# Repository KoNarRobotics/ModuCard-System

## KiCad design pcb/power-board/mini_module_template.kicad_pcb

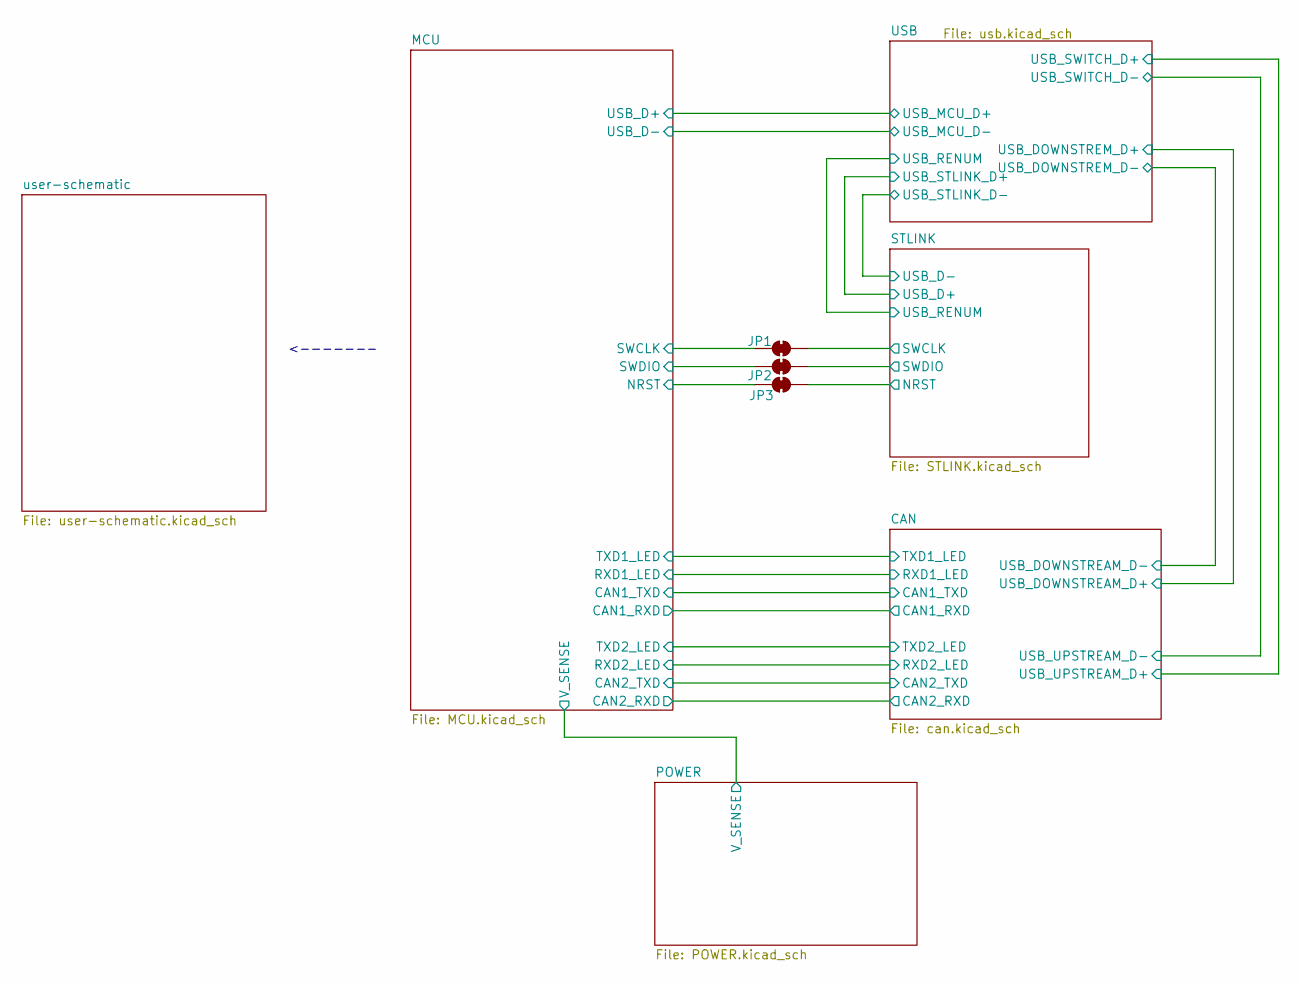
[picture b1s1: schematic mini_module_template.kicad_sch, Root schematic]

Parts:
JP1, JP2, JP3: SolderJumper_2_Bridged; SolderJumper-2_P1.3mm_Open_RoundedPad1.0x1.5mm

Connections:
/MCU/NRST: JP3.1 (A); also elsewhere on the board
/MCU/SWCLK: JP1.1 (A); also elsewhere on the board
/MCU/SWDIO: JP2.1 (A); also elsewhere on the board
/STLINK/NRST: JP3.2 (B); also elsewhere on the board
/STLINK/SWCLK: JP1.2 (B); also elsewhere on the board
/STLINK/SWDIO: JP2.2 (B); also elsewhere on the board

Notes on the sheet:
<-------

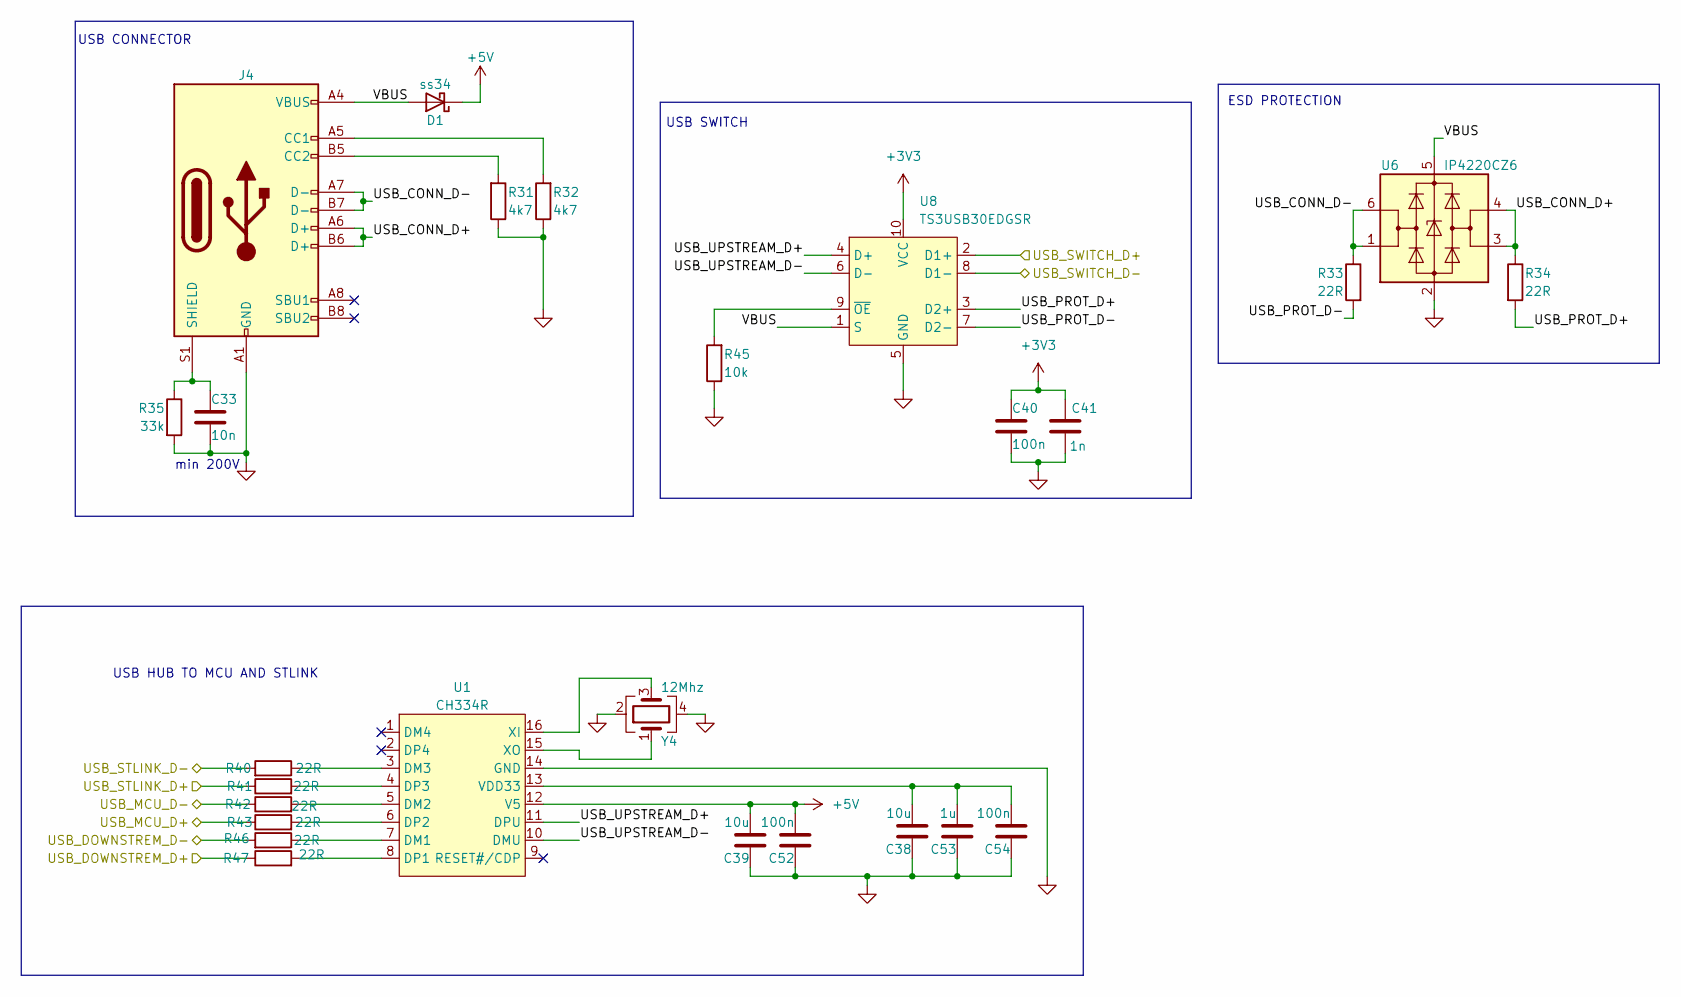
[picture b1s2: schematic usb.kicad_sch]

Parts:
C33: 10n; C_0402_1005Metric
C38, C39: 10u; C_0603_1608Metric
C40, C54: 100n; C_0402_1005Metric
C41: 1n; C_0402_1005Metric
C52: 100n; C_0603_1608Metric
C53: 1u; C_0603_1608Metric
D1: ss34; D_SMA
J4: USB_C_Receptacle_USB2.0; USB_C_Receptacle_G-Switch_GT-USB-7010ASV
R31, R32: 4k7; R_0402_1005Metric
R33, R34, R40, R41, R42, R43, R46, R47: 22R; R_0402_1005Metric
R35: 33k; R_0402_1005Metric
R45: 10k; R_0402_1005Metric
U1: CH334R; QSOP-16_3.9x4.9mm_P0.635mm
U6: IP4220CZ6; SOT-23-6
U8: TS3USB30EDGSR; VSSOP-10_3x3mm_P0.5mm
Y4: 12Mhz; Crystal_SMD_3225-4Pin_3.2x2.5mm

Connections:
+3V3: C40.1, C41.1, U8.10 (VCC); also elsewhere on the board
+5V: C39.2, C52.2, D1.1 (K), U1.12 (V5); also elsewhere on the board
/CAN/USB_DOWNSTREAM_D+: R47.1; also elsewhere on the board
/CAN/USB_DOWNSTREAM_D-: R46.2; also elsewhere on the board
/CAN/USB_UPSTREAM_D+: U8.2 (D1+); also elsewhere on the board
/CAN/USB_UPSTREAM_D-: U8.8 (D1-); also elsewhere on the board
/MCU/USB_D+: R43.1; also elsewhere on the board
/MCU/USB_D-: R42.1; also elsewhere on the board
/STLINK/USB_D+: R41.1; also elsewhere on the board
/STLINK/USB_D-: R40.2; also elsewhere on the board
/USB/USB_CONN_D+: J4.A6 (D+), J4.B6 (D+), R34.1, U6.3 (I/O2), U6.4 (I/O2)
/USB/USB_CONN_D-: J4.A7 (D-), J4.B7 (D-), R33.1, U6.1 (I/O1), U6.6 (I/O1)
/USB/USB_PROT_D+: R34.2, U8.3 (D2+)
/USB/USB_PROT_D-: R33.2, U8.7 (D2-)
/USB/USB_UPSTREAM_D+: U1.11 (DPU), U8.4 (D+)
/USB/USB_UPSTREAM_D-: U1.10 (DMU), U8.6 (D-)
/USB/VBUS: D1.2 (A), J4.A4 (VBUS), J4.A9 (VBUS), J4.B4 (VBUS), J4.B9 (VBUS), U6.5 (VBUS), U8.1 (S)
GND: C33.2, C38.1, C39.1, C40.2, C41.2, C52.1, C53.1, C54.1, J4.A1 (GND), J4.A12 (GND), J4.B1 (GND), J4.B12 (GND), R31.1, R32.1, R35.2, R45.1, U1.14 (GND), U6.2 (GND), U8.5 (GND), Y4.2, Y4.4; also elsewhere on the board
unnamed: J4.A5 (CC1), R32.2
unnamed: J4.B5 (CC2), R31.2
unnamed: C33.1, J4.S1 (SHIELD), R35.1
unnamed: R46.1, U1.7 (DM1)
unnamed: R42.2, U1.5 (DM2)
unnamed: R40.1, U1.3 (DM3)
unnamed: R47.2, U1.8 (DP1)
unnamed: R43.2, U1.6 (DP2)
unnamed: R41.2, U1.4 (DP3)
unnamed: C38.2, C53.2, C54.2, U1.13 (VDD33)
unnamed: U1.16 (XI), Y4.3
unnamed: U1.15 (XO), Y4.1
unnamed: R45.2, U8.9 (~OE)

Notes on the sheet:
USB SWITCH
USB CONNECTOR
USB HUB TO MCU AND STLINK
ESD PROTECTION
min 200V

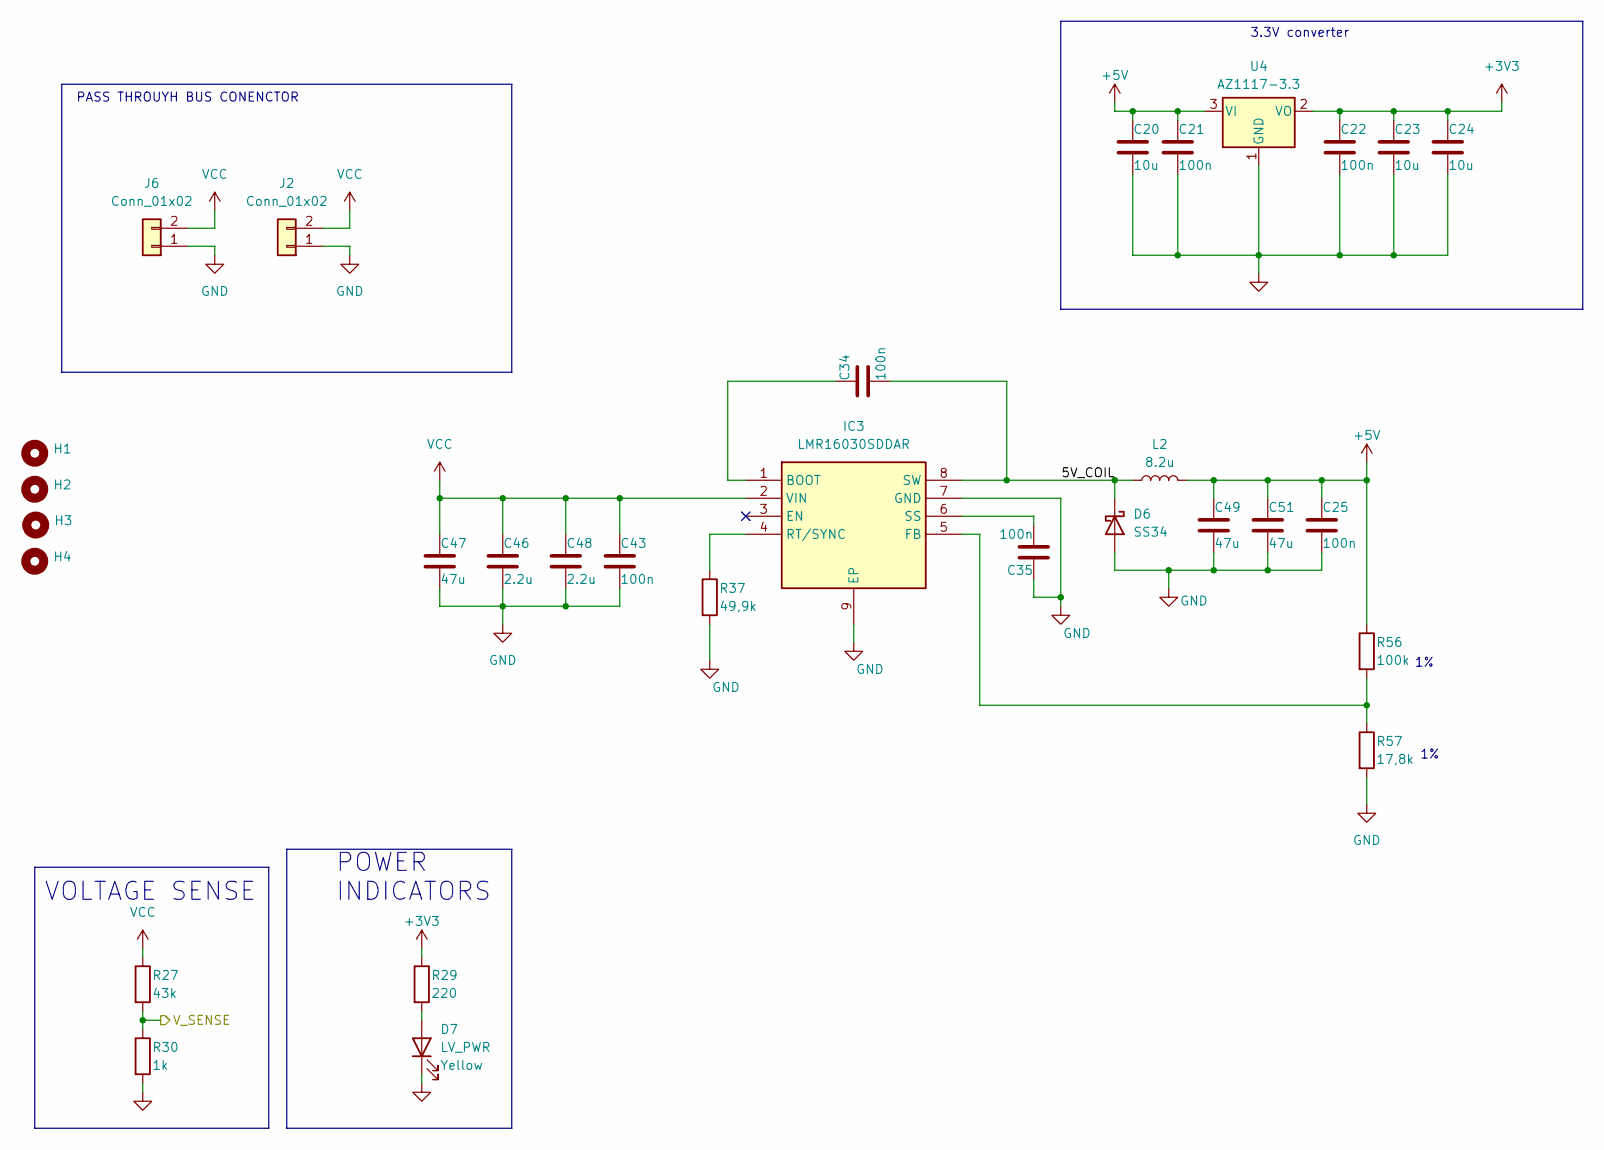
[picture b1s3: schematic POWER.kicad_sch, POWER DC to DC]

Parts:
C20, C23, C24: 10u; C_0805_2012Metric
C21, C25, C34, C35, C43: 100n; C_0402_1005Metric
C22: 100n; C_0603_1608Metric
C46, C48: 2.2u; C_1206_3216Metric
C47: 47u; C_Elec_10x10.2
C49, C51: 47u; C_1206_3216Metric
D6: SS34; D_SMA
D7: LV_PWR; D_0603_1608Metric
H1, H2, H3, H4: MountingHole_3.2mm_M3
IC3: LMR16030SDDAR; SOIC127P600X170-9N; Manufacturer_Part_Number LMR16030SDDAR; Mouser Part Number 595-LMR16030SDDAR
J2, J6: Conn_01x02; AMASS_XT60PW-M_1x02_P7.20mm_Horizontal
L2: 8.2u; L_Cenker_CKCS6045
R27: 43k; R_0402_1005Metric
R29: 220; R_0402_1005Metric
R30: 1k; R_0402_1005Metric
R37: 49,9k; R_0402_1005Metric
R56: 100k; R_0402_1005Metric
R57: 17,8k; R_0402_1005Metric
U4: AZ1117-3.3; SOT-223-3_TabPin2

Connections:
+3V3: C22.1, C23.1, C24.1, R29.1, U4.2 (VO); also elsewhere on the board
+5V: C20.1, C21.1, C25.1, C49.1, C51.1, L2.2, R56.1, U4.3 (VI); also elsewhere on the board
/MCU/V_SENSE: R27.2, R30.1; also elsewhere on the board
/POWER/5V_COIL: C34.2, D6.1 (K), IC3.8 (SW), L2.1
GND: C20.2, C21.2, C22.2, C23.2, C24.2, C25.2, C35.1, C43.2, C46.2, C47.2, C48.2, C49.2, C51.2, D6.2 (A), D7.1 (K), IC3.7 (GND), IC3.9 (EP), J2.1, J6.1, R30.2, R37.2, R57.2, U4.1 (GND); also elsewhere on the board
unnamed: D7.2 (A), R29.2
unnamed: C34.1, IC3.1 (BOOT)
unnamed: IC3.5 (FB), R56.2, R57.1
unnamed: IC3.4 (RT/SYNC), R37.1
unnamed: C35.2, IC3.6 (SS)
VCC: C43.1, C46.1, C47.1, C48.1, IC3.2 (VIN), J2.2, J6.2, R27.1

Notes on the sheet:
VOLTAGE SENSE
PASS THROUYH BUS CONENCTOR
POWER INDICATORS
3.3V converter

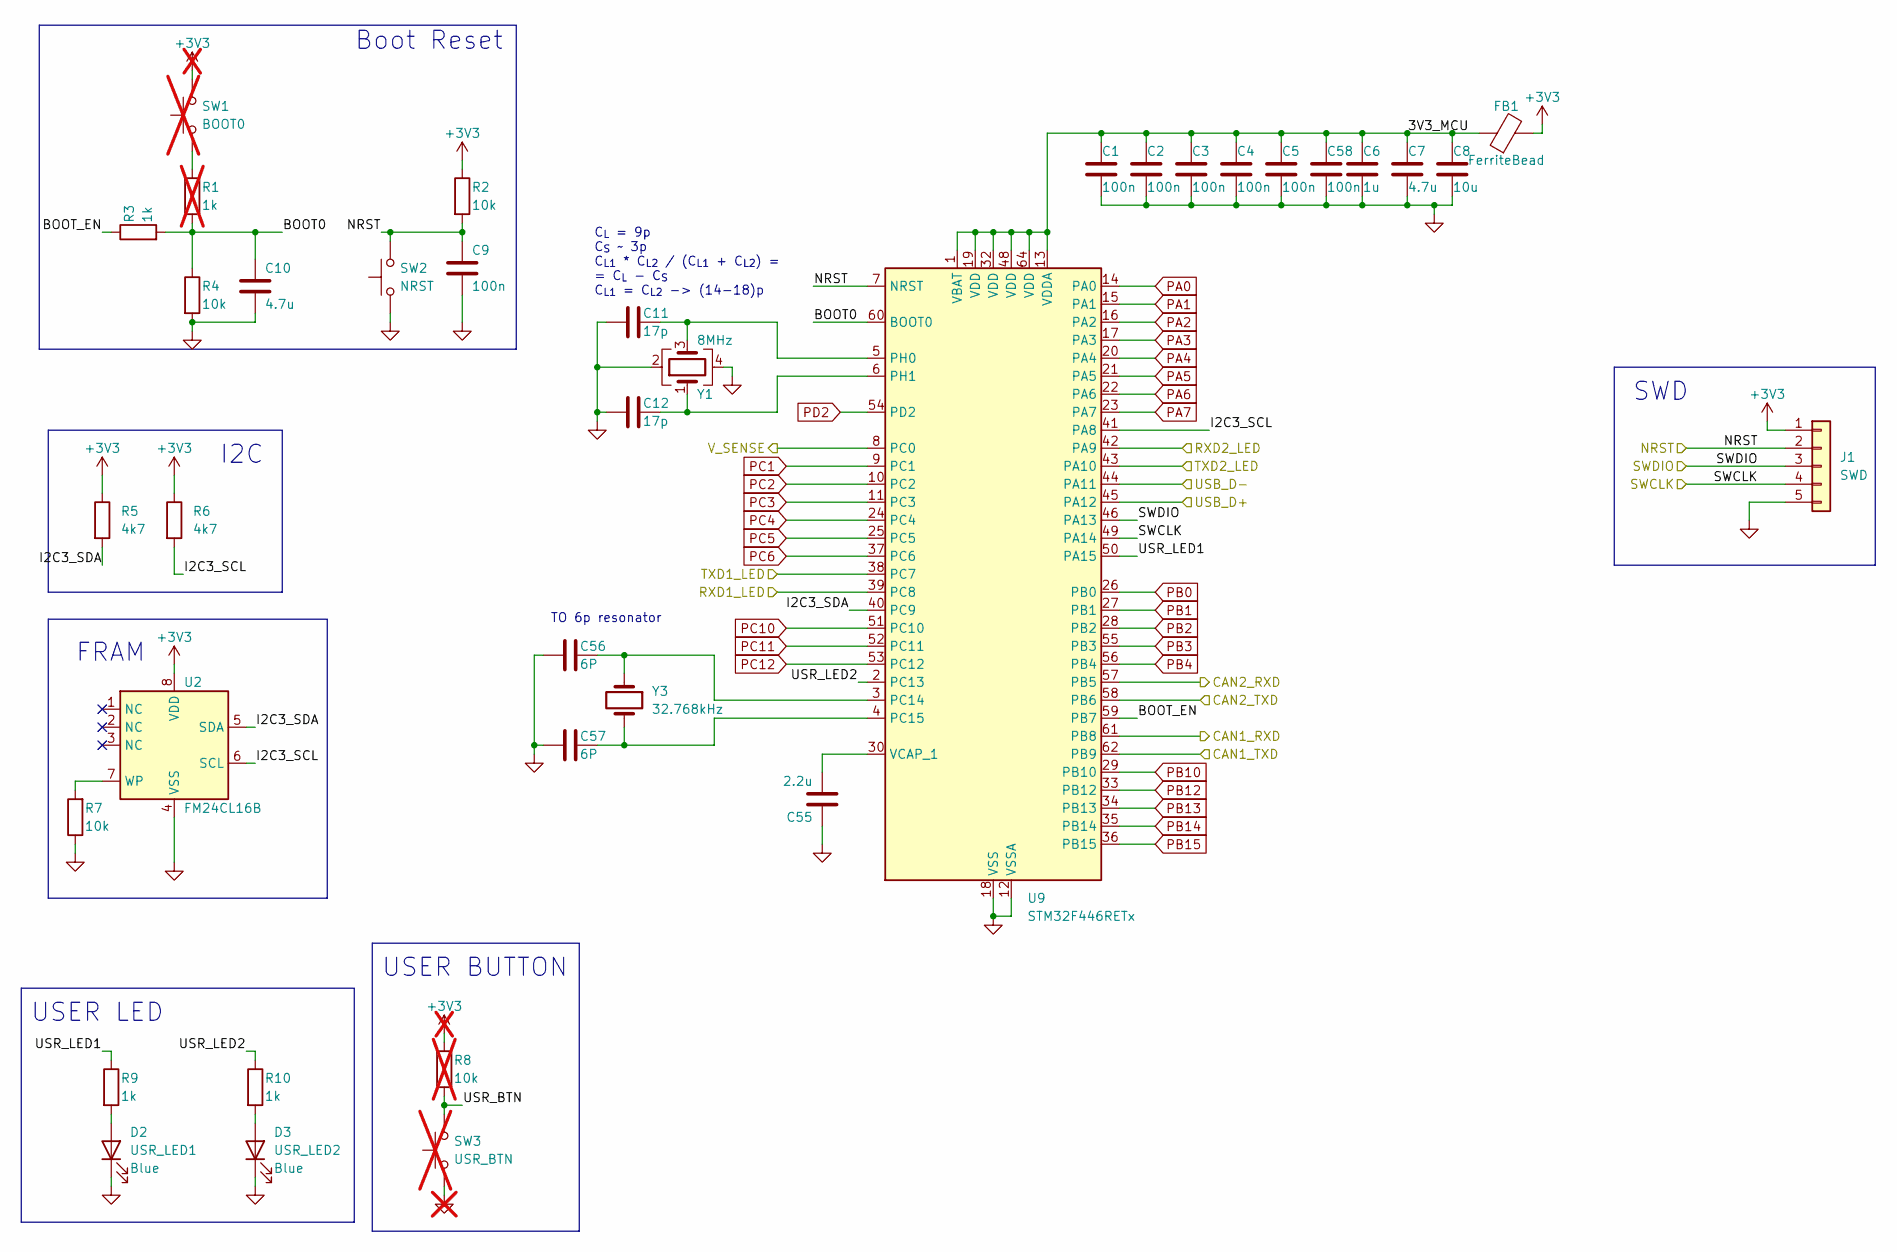
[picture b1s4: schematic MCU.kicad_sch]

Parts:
C1, C2, C3, C4, C5, C9, C58: 100n; C_0402_1005Metric
C6: 1u; C_0603_1608Metric
C7: 4.7u; C_0603_1608Metric
C8: 10u; C_0805_2012Metric
C10: 4.7u; C_0402_1005Metric
C11, C12: 17p; C_0402_1005Metric
C55: 2.2u; C_0402_1005Metric
C56, C57: 6P; C_0402_1005Metric
D2: USR_LED1; D_0603_1608Metric
D3: USR_LED2; D_0603_1608Metric
FB1: FerriteBead; L_0805_2012Metric
J1: SWD; PinSocket_1x05_P2.54mm_Vertical
R1: 1k; R_0402_1005Metric; not fitted
R2, R4, R7: 10k; R_0402_1005Metric
R3, R9, R10: 1k; R_0402_1005Metric
R5, R6: 4k7; R_0402_1005Metric
R8: 10k; R_0402_1005Metric; not fitted
SW1: BOOT0; SW_Tactile_SPST_Angled_PTS645Vx58-2LFS; not fitted
SW2: NRST; SW_Tactile_SPST_Angled_PTS645Vx58-2LFS
SW3: USR_BTN; SW_Tactile_SPST_Angled_PTS645Vx58-2LFS; not fitted
U2: FM24CL16B; SOIC-8_3.9x4.9mm_P1.27mm
U9: STM32F446RETx; LQFP-64_10x10mm_P0.5mm
Y1: 8MHz; Crystal_SMD_3225-4Pin_3.2x2.5mm
Y3: 32.768kHz; Crystal_SMD_3215-2Pin_3.2x1.5mm

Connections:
+3V3: FB1.2, J1.1, R2.1, R5.1, R6.1, R8.1, SW1.2, U2.8 (VDD); also elsewhere on the board
/CAN/CAN1_RXD: U9.61 (PB8); also elsewhere on the board
/CAN/CAN1_TXD: U9.62 (PB9); also elsewhere on the board
/CAN/CAN2_RXD: U9.57 (PB5); also elsewhere on the board
/CAN/CAN2_TXD: U9.58 (PB6); also elsewhere on the board
/CAN/RXD1_LED: U9.39 (PC8); also elsewhere on the board
/CAN/RXD2_LED: U9.42 (PA9); also elsewhere on the board
/CAN/TXD1_LED: U9.38 (PC7); also elsewhere on the board
/CAN/TXD2_LED: U9.43 (PA10); also elsewhere on the board
/MCU/3V3_MCU: C1.1, C2.1, C3.1, C4.1, C5.1, C6.1, C7.1, C8.1, C58.1, FB1.1, U9.1 (VBAT), U9.13 (VDDA), U9.19 (VDD), U9.32 (VDD), U9.48 (VDD), U9.64 (VDD)
/MCU/BOOT0: C10.1, R1.2, R3.2, R4.1, U9.60 (BOOT0)
/MCU/BOOT_EN: R3.1, U9.59 (PB7)
/MCU/I2C3_SCL: R6.2, U2.6 (SCL), U9.41 (PA8)
/MCU/I2C3_SDA: R5.2, U2.5 (SDA), U9.40 (PC9)
/MCU/NRST: C9.1, J1.2, R2.2, SW2.2, U9.7 (NRST); also elsewhere on the board
/MCU/SWCLK: J1.4, U9.49 (PA14); also elsewhere on the board
/MCU/SWDIO: J1.3, U9.46 (PA13); also elsewhere on the board
/MCU/USB_D+: U9.45 (PA12); also elsewhere on the board
/MCU/USB_D-: U9.44 (PA11); also elsewhere on the board
/MCU/USR_LED1: R9.1, U9.50 (PA15)
/MCU/USR_LED2: R10.1, U9.2 (PC13)
/MCU/V_SENSE: U9.8 (PC0); also elsewhere on the board
GND: C1.2, C2.2, C3.2, C4.2, C5.2, C6.2, C7.2, C8.2, C9.2, C10.2, C11.1, C12.1, C55.1, C56.1, C57.1, C58.2, D2.1 (K), D3.1 (K), J1.5, R4.2, R7.1, SW2.1, SW3.1, U2.4 (VSS), U9.12 (VSSA), U9.18 (VSS), U9.31 (VSS), U9.47 (VSS), U9.63 (VSS), Y1.2, Y1.4; also elsewhere on the board
unnamed: D2.2 (A), R9.2
unnamed: D3.2 (A), R10.2
unnamed: R1.1, SW1.1
unnamed: R8.2, SW3.2
unnamed: R7.2, U2.7 (WP)
unnamed: C56.2, U9.3 (PC14), Y3.1
unnamed: C57.2, U9.4 (PC15), Y3.2
unnamed: C11.2, U9.5 (PH0), Y1.3
unnamed: C12.2, U9.6 (PH1), Y1.1
unnamed: C55.2, U9.30 (VCAP_1)
PA0: U9.14 (PA0)
PA1: U9.15 (PA1)
PA2: U9.16 (PA2)
PA3: U9.17 (PA3)
PA4: U9.20 (PA4)
PA5: U9.21 (PA5)
PA6: U9.22 (PA6)
PA7: U9.23 (PA7)
PB0: U9.26 (PB0)
PB1: U9.27 (PB1)
PB2: U9.28 (PB2)
PB3: U9.55 (PB3)
PB4: U9.56 (PB4)
PB10: U9.29 (PB10)
PB12: U9.33 (PB12)
PB13: U9.34 (PB13)
PB14: U9.35 (PB14)
PB15: U9.36 (PB15)
PC1: U9.9 (PC1)
PC2: U9.10 (PC2)
PC3: U9.11 (PC3)
PC4: U9.24 (PC4)
PC5: U9.25 (PC5)
PC6: U9.37 (PC6)
PC10: U9.51 (PC10)
PC11: U9.52 (PC11)
PC12: U9.53 (PC12)
PD2: U9.54 (PD2)

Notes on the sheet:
SWD
I2C
USER BUTTON
TO 6p resonator
FRAM
C_{L} = 9p C_{S} ~ 3p C_{L1} * C_{L2} / (C_{L1} + C_{L2}) = = C_{L} - C_{S} C_{L1} = C_{L2} -> (14-18)p
USER LED
Boot Reset

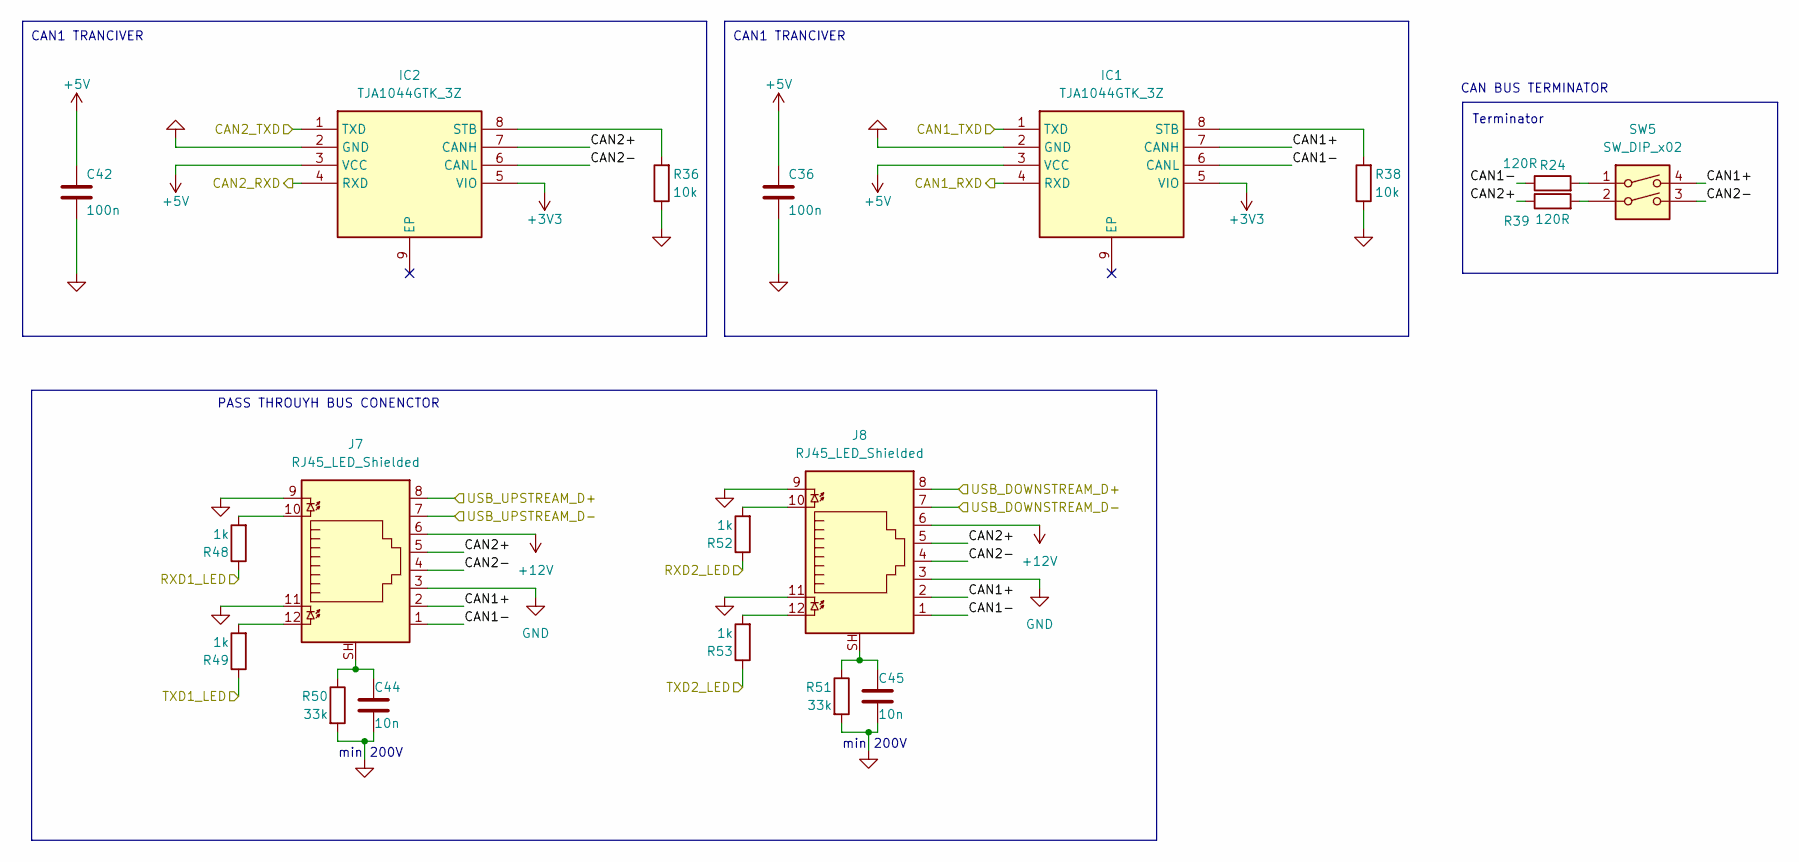
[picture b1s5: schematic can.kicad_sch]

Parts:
C36, C42: 100n; C_0402_1005Metric
C44, C45: 10n; C_0402_1005Metric
IC1, IC2: TJA1044GTK_3Z; SON65P300X300X100-9N-D; Manufacturer_Part_Number TJA1044GTK/3Z; Mouser Part Number 771-TJA1044GTK/3Z
J7, J8: RJ45_LED_Shielded; RJ45_Amphenol_RJHSE538X
R24, R39: 120R; R_0603_1608Metric
R36, R38: 10k; R_0402_1005Metric
R48, R49, R52, R53: 1k; R_0402_1005Metric
R50, R51: 33k; R_0402_1005Metric
SW5: SW_DIP_x02; SW_DIP_SPSTx02_Slide_6.7x6.64mm_W7.62mm_P2.54mm_LowProfile

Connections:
+3V3: IC1.5 (VIO), IC2.5 (VIO); also elsewhere on the board
+5V: C36.1, C42.1, IC1.3 (VCC), IC2.3 (VCC); also elsewhere on the board
+12V: J7.6, J8.6
/CAN/CAN1+: IC1.7 (CANH), J7.2, J8.2, SW5.4
/CAN/CAN1-: IC1.6 (CANL), J7.1, J8.1, R24.1
/CAN/CAN1_RXD: IC1.4 (RXD); also elsewhere on the board
/CAN/CAN1_TXD: IC1.1 (TXD); also elsewhere on the board
/CAN/CAN2+: IC2.7 (CANH), J7.5, J8.5, R39.1
/CAN/CAN2-: IC2.6 (CANL), J7.4, J8.4, SW5.3
/CAN/CAN2_RXD: IC2.4 (RXD); also elsewhere on the board
/CAN/CAN2_TXD: IC2.1 (TXD); also elsewhere on the board
/CAN/RXD1_LED: R48.1; also elsewhere on the board
/CAN/RXD2_LED: R52.1; also elsewhere on the board
/CAN/TXD1_LED: R49.1; also elsewhere on the board
/CAN/TXD2_LED: R53.1; also elsewhere on the board
/CAN/USB_DOWNSTREAM_D+: J8.8; also elsewhere on the board
/CAN/USB_DOWNSTREAM_D-: J8.7; also elsewhere on the board
/CAN/USB_UPSTREAM_D+: J7.8; also elsewhere on the board
/CAN/USB_UPSTREAM_D-: J7.7; also elsewhere on the board
GND: C36.2, C42.2, C44.2, C45.2, IC1.2 (GND), IC2.2 (GND), J7.3, J7.9, J7.11, J8.3, J8.9, J8.11, R36.1, R38.1, R50.2, R51.2; also elsewhere on the board
unnamed: C44.1, J7.SH, R50.1
unnamed: C45.1, J8.SH, R51.1
unnamed: IC1.8 (STB), R38.2
unnamed: IC2.8 (STB), R36.2
unnamed: J7.10, R48.2
unnamed: J7.12, R49.2
unnamed: J8.10, R52.2
unnamed: J8.12, R53.2
unnamed: R24.2, SW5.1
unnamed: R39.2, SW5.2

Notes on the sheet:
min 200V
CAN1 TRANCIVER
PASS THROUYH BUS CONENCTOR
Terminator
CAN BUS TERMINATOR

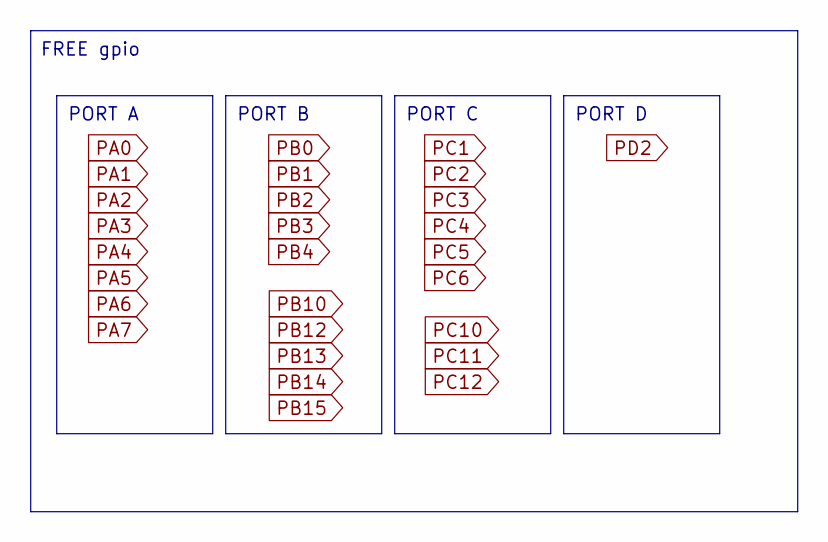
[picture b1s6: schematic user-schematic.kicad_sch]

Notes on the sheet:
PORT D
PORT B
PORT C
PORT A
FREE gpio

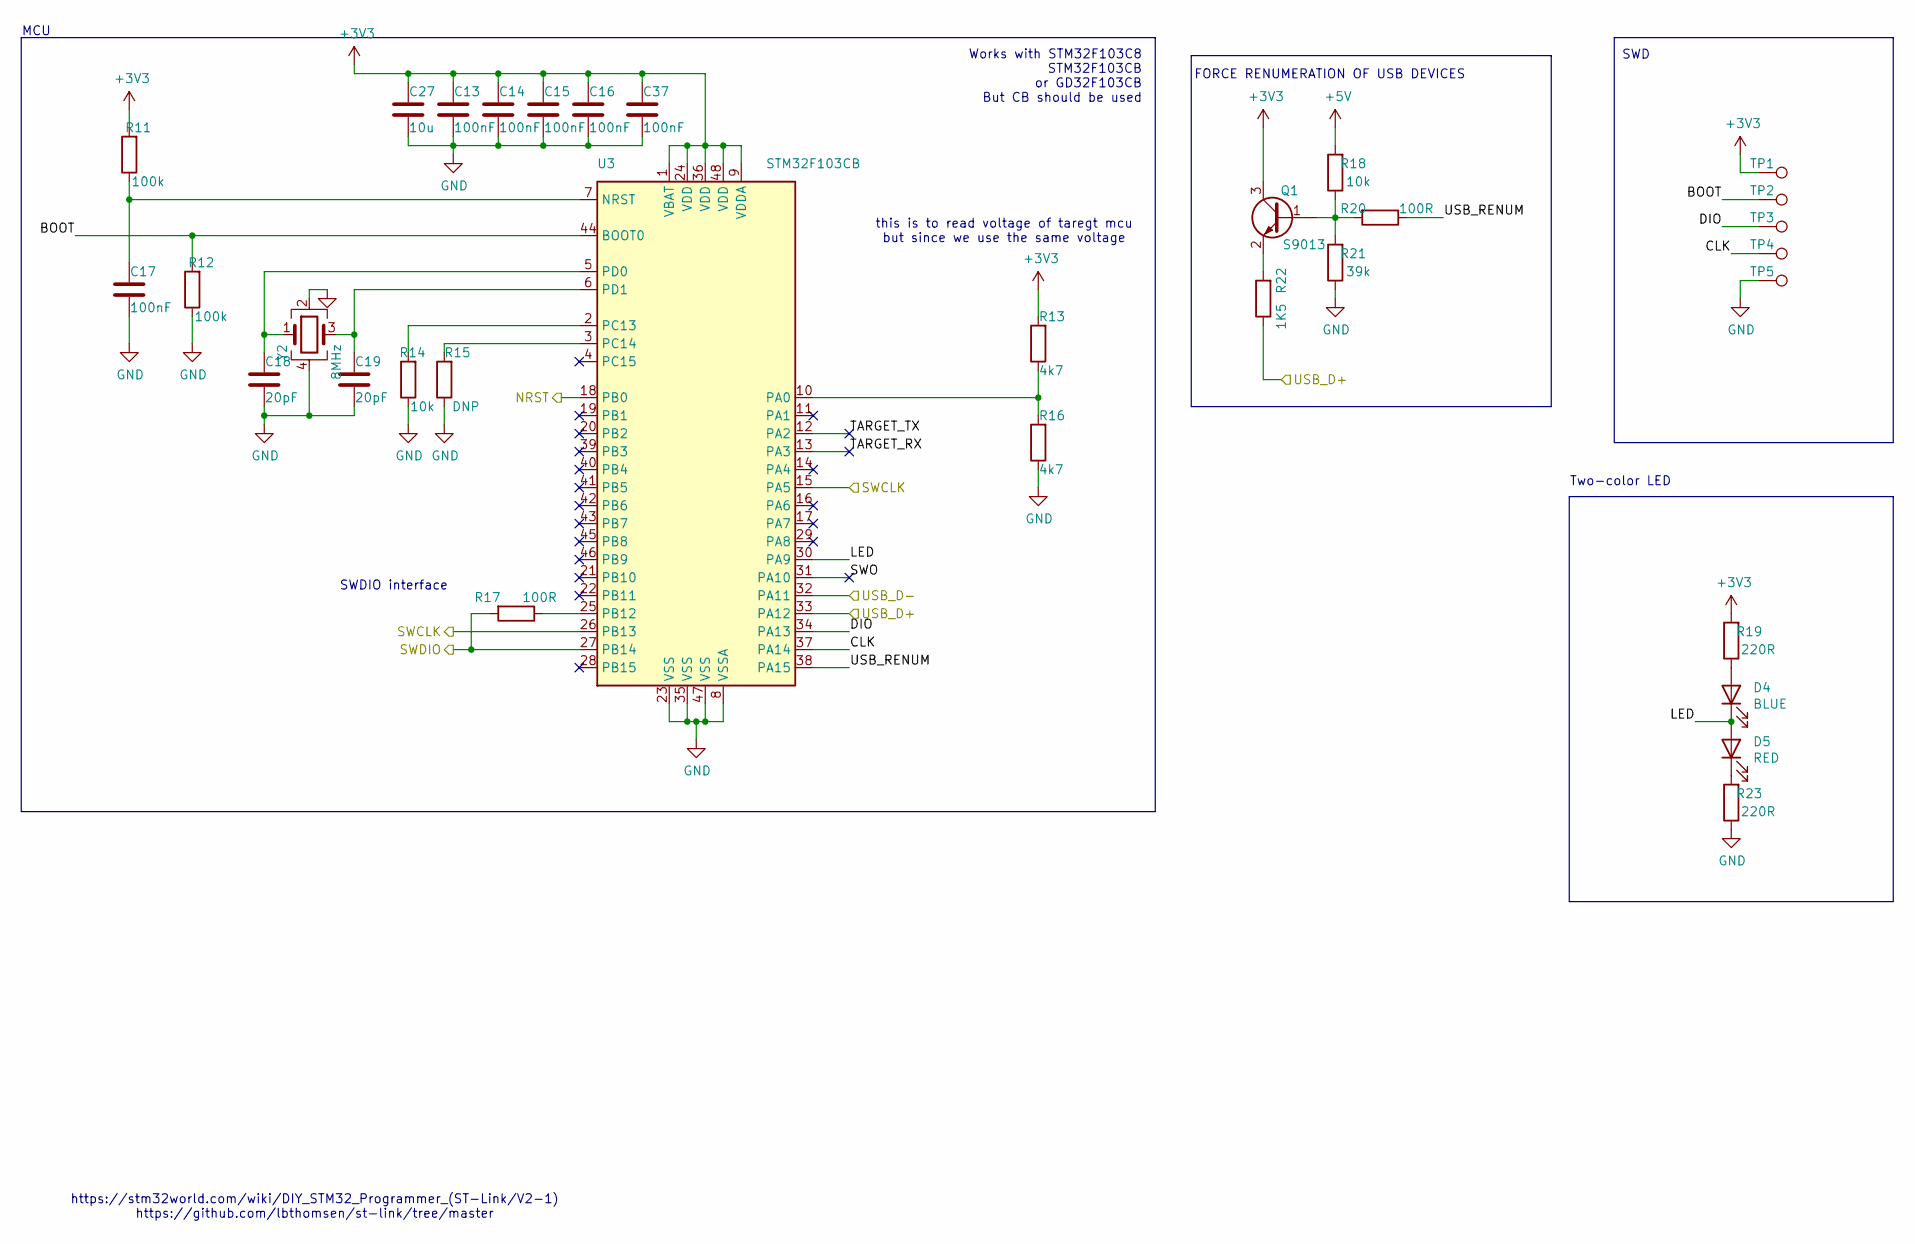
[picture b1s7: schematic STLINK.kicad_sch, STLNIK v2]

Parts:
C13, C14, C15, C16, C17, C37: 100nF; C_0402_1005Metric; LCSC C1525
C18, C19: 20pF; C_0402_1005Metric; LCSC C1554
C27: 10u; C_0805_2012Metric
D4: BLUE; LED_0603_1608Metric; LCSC C72041
D5: RED; LED_0603_1608Metric; LCSC C2286
Q1: S9013; SOT-23; LCSC C6749
R11, R12: 100k; R_0402_1005Metric; LCSC C25741
R13, R16: 4k7; R_0402_1005Metric; LCSC C25900
R14, R18: 10k; R_0402_1005Metric; LCSC C25744
R15: DNP; R_0402_1005Metric; LCSC xxC25744
R17: 100R; R_0603_1608Metric; LCSC C25076
R19, R23: 220R; R_0402_1005Metric; LCSC C25091
R20: 100R; R_0402_1005Metric; LCSC C25076
R21: 39k; R_0402_1005Metric; LCSC C25783
R22: 1K5; R_0402_1005Metric; LCSC C25867
TP1, TP2, TP3, TP4, TP5: TestPoint_Pad_1.0x1.0mm
U3: STM32F103CB; LQFP-48_7x7mm_P0.5mm; LCSC C8304
Y2: 8MHz; Crystal_SMD_3225-4Pin_3.2x2.5mm

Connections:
+3V3: C13.1, C14.1, C15.1, C16.1, C27.1, C37.1, Q1.3 (C), R11.2, R13.2, R19.2, TP1.1, U3.1 (VBAT), U3.9 (VDDA), U3.24 (VDD), U3.36 (VDD), U3.48 (VDD); also elsewhere on the board
+5V: R18.2; also elsewhere on the board
/STLINK/BOOT: R12.2, TP2.1, U3.44 (BOOT0)
/STLINK/CLK: TP4.1, U3.37 (PA14)
/STLINK/DIO: TP3.1, U3.34 (PA13)
/STLINK/LED: D4.1 (K), D5.2 (A), U3.30 (PA9)
/STLINK/NRST: U3.18 (PB0); also elsewhere on the board
/STLINK/SWCLK: U3.15 (PA5), U3.26 (PB13); also elsewhere on the board
/STLINK/SWDIO: R17.2, U3.27 (PB14); also elsewhere on the board
/STLINK/SWO: U3.31 (PA10)
/STLINK/TARGET_RX: U3.13 (PA3)
/STLINK/TARGET_TX: U3.12 (PA2)
/STLINK/USB_D+: R22.1, U3.33 (PA12); also elsewhere on the board
/STLINK/USB_D-: U3.32 (PA11); also elsewhere on the board
/STLINK/USB_RENUM: R20.1, U3.38 (PA15)
GND: C13.2, C14.2, C15.2, C16.2, C17.2, C18.2, C19.2, C27.2, C37.2, R12.1, R14.1, R15.1, R16.1, R21.1, R23.1, TP5.1, U3.8 (VSSA), U3.23 (VSS), U3.35 (VSS), U3.47 (VSS), Y2.2, Y2.4; also elsewhere on the board
unnamed: D4.2 (A), R19.1
unnamed: D5.1 (K), R23.2
unnamed: Q1.1 (B), R18.1, R20.2, R21.2
unnamed: Q1.2 (E), R22.2
unnamed: C17.1, R11.1, U3.7 (NRST)
unnamed: R13.1, R16.2, U3.10 (PA0)
unnamed: R17.1, U3.25 (PB12)
unnamed: R14.2, U3.2 (PC13)
unnamed: R15.2, U3.3 (PC14)
unnamed: C18.1, U3.5 (PD0), Y2.1
unnamed: C19.1, U3.6 (PD1), Y2.3

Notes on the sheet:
this is to read voltage of taregt mcu but since we use the same voltage
https://stm32world.com/wiki/DIY_STM32_Programmer_(ST-Link/V2-1) https://github.com/lbthomsen/st-link/tree/master
SWDIO interface
Works with STM32F103C8 STM32F103CB or GD32F103CB But CB should be used
FORCE RENUMERATION OF USB DEVICES
MCU
Two-color LED
SWD

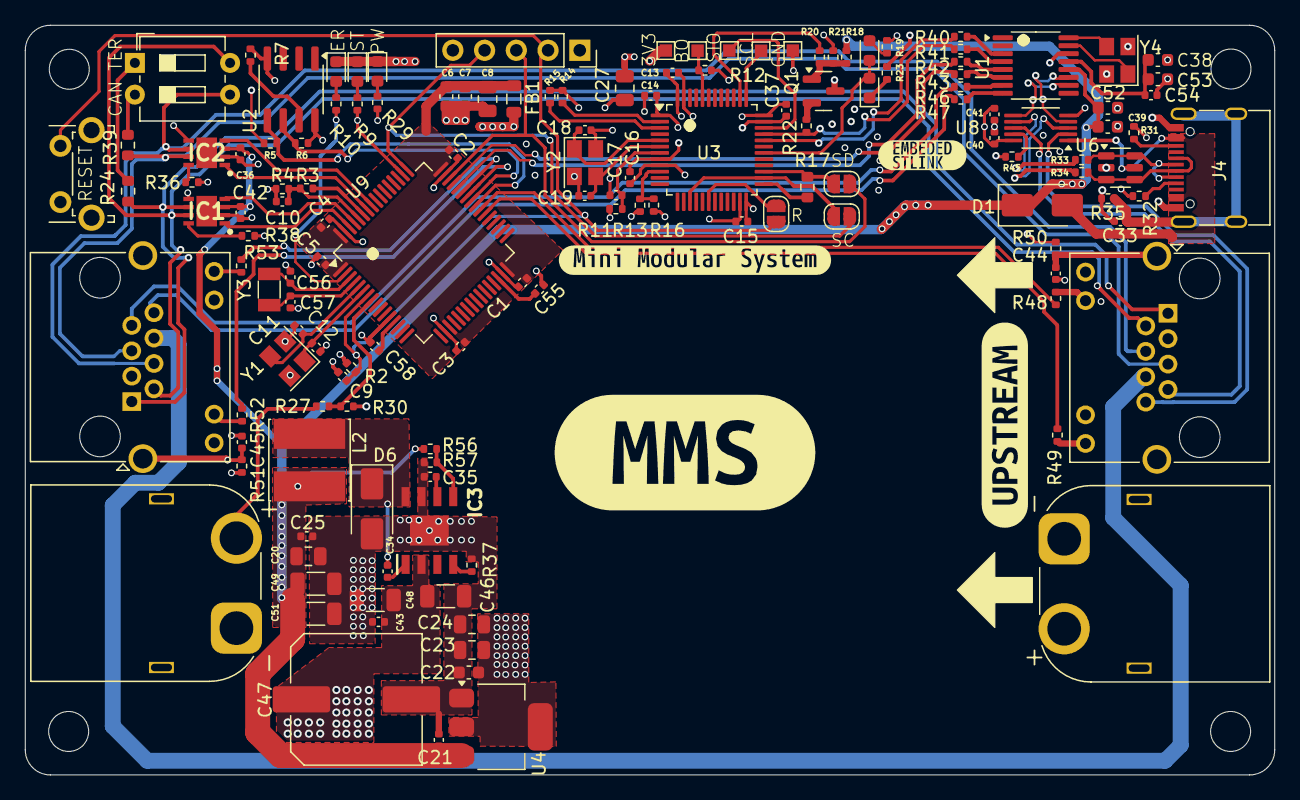
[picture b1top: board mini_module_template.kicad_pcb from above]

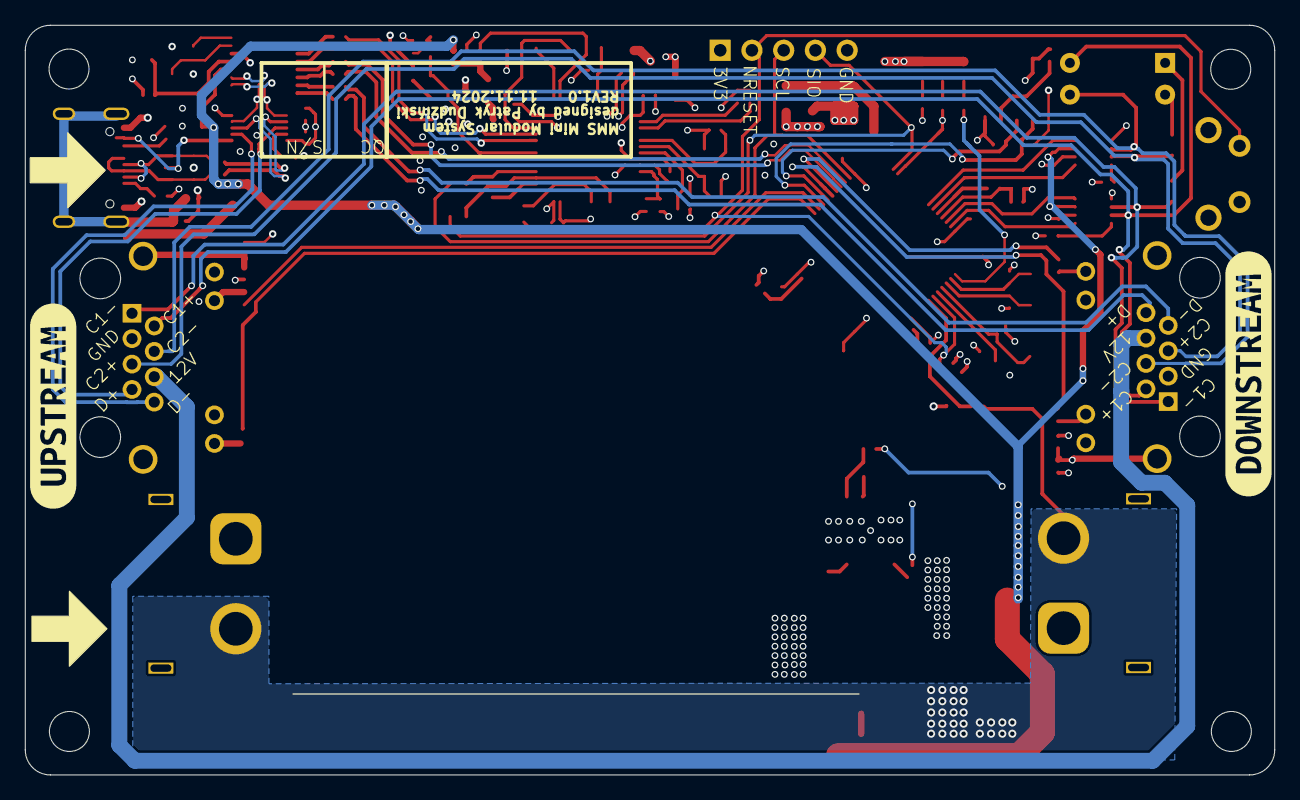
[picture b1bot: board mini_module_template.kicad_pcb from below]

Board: 4 copper layers, 100.0 x 60.0 mm, 150 parts (2 on the bottom side), 99 nets.

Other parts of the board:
kibuzzard-674CE2D2: G***; kibuzzard-674CE2D2
kibuzzard-67314D46: G***; kibuzzard-67314D46
kibuzzard-673147F0, kibuzzard-673147F0#2: G***; kibuzzard-673147F0
kibuzzard-673151BF: G***; kibuzzard-673151BF
kibuzzard-67314807: G***; kibuzzard-67314807

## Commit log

2024-12-29 Add CI, remove trash
2024-12-29 Trigger CI on push
2024-12-29 Uploat artifacts on failure
2024-12-29 Upload everything as artifact, change test KiCad project
2024-12-29 Add backplane project back
2024-12-29 Add mini modular as test
2024-12-29 Add generated schematic PDF, necessary Gerber layers, and 3D model
2024-12-29 Add generated blend model of backplane
